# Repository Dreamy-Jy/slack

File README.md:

This is a repo containing all docs related to Slack, a custom plank style keyboard meant for being used while relaxing.

There are 2 prototype revisions planned, each one getting closer to my ideal. Experimental modules will be hosted here as well.

Any revisions pass the second revision will be for refinements.

Why are components rated differently?
- Caps have a voltage rating
- Resistor have a power dissipation rating

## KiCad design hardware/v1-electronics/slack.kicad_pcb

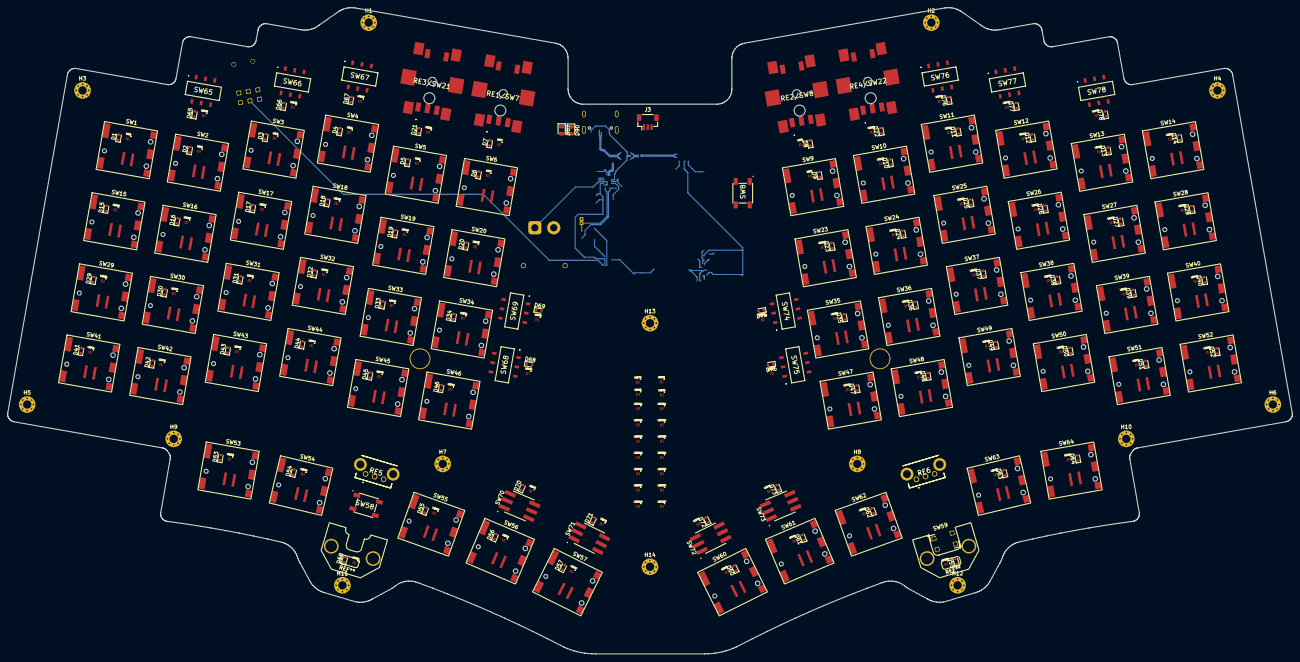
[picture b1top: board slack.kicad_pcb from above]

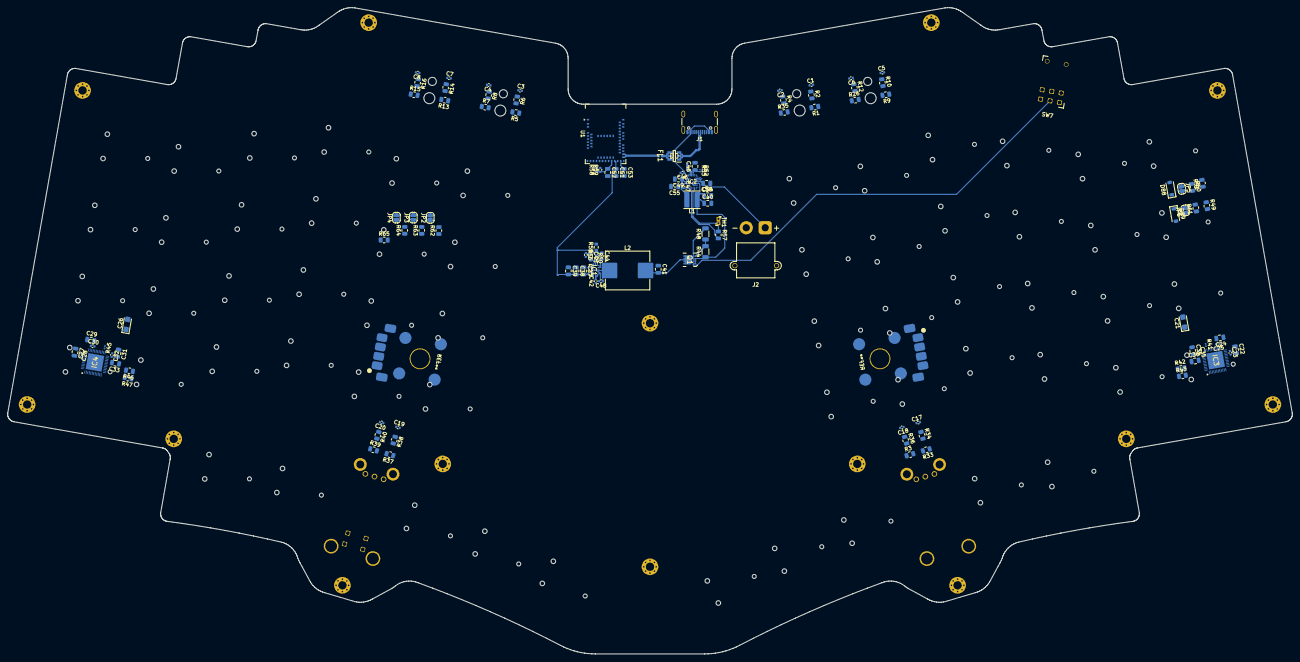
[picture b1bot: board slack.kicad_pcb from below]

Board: 4 copper layers, 338.9 x 170.5 mm, 388 parts (116 on the bottom side), 215 nets.

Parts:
C1, C2, C3, C4, C5, C6, C7, C8, C17, C18, C19, C20: 0.01μF; C_0402_1005Metric
C21, C26: 22μF; CP_EIA-3216-18_Kemet-A
C22, C24, C27, C29, C31, C33, C34, C36: 0.47μF; C_0805_2012Metric
C23, C25, C28, C30, C32, C35, C42, C48: 0.1μF; C_0402_1005Metric
C37, C38, C39: 22μF; C_0805_2012Metric
C40, C41, C49, C50, C51, C52, C53, C54, C55: 10μF; C_0805_2012Metric
C43: 1μF; C_0402_1005Metric
C44: 2.20μF; C_0603_1608Metric
C45: 2.2nF; C_0603_1608Metric
C46: 4.7μF; C_0805_2012Metric
C47: 22nF; C_0402_1005Metric
D0: USBLC6-2SC6; SOT95P280X145-6N
D1, D2, D3, D4, D5, D6, D7, D8, D9, D10, D11, D12, D13, D14, D15, D16, D17, D18, D19, D20, D21, D22, D23, D24, D25, D26, D27, D28, D29, D30, D31, D32, D33, D34, D35, D36, D37, D38, D39, D40, D41, D42, D43, D44, D45, D46, D47, D48, D49, D50, D51, D52, D53, D54, D55, D56, D57, D58, D59, D60, D61, D62, D63, D64, D65, D66, D67, D68, D69, D70, D71, D72, D73, D74, D75, D76, D77, D78: BAS16TS; D_SOD-523
D87, D90: LED_Small_Filled; LED_0805_2012Metric
D88, D89: 3.6V; D_SOD-123
FL1: EXC14CE900U
H1, H2, H3, H4, H5, H6, H7, H8, H9, H10, H11, H12, H13, H14: MountingHole_2.2mm_M2_Pad_Via
IC1: TPS61288LRQQR; PTPS61288RQQR
IC2: MP2721GRH-0000-Z; QFN-22_MP2721_MNP
IC3, IC4: IS31FL3733-QFLS4-TR; QFN40P600X600X80-49N-D
J1: USB4105-GF-A-120; USB_C_Receptacle_GCT_USB4105-xx-A_16P_TopMnt_Horizontal
J2: XT30PW-M; AMASS_XT30PW-M_1x02_P2.50mm_Horizontal_Tight
J3: Female JST-SH; JST_SH_BM03B-SRSS-TB_1x03-1MP_P1.00mm_Vertical
JP2, JP3, JP4, JP5, JP6: Jumper_2_Small_Open; SolderJumper-2_P1.3mm_Open_RoundedPad1.0x1.5mm
L1: 1μH; L_Changjiang_FTC404030S
L2: 2.20μH; L_Sunlord_MWSA1005S
LED1, LED2, LED3, LED4, LED5, LED6, LED7, LED8, LED9, LED10, LED11, LED12, LED13, LED14, LED15, LED16, LED17, LED18, LED19, LED20, LED21, LED22, LED23, LED24, LED25, LED26, LED27, LED28, LED29, LED30, LED31, LED32, LED33, LED34, LED35, LED36, LED37, LED38, LED39, LED40, LED41, LED42, LED43, LED44, LED45, LED46, LED47, LED48, LED49, LED50, LED51, LED52, LED53, LED54, LED55, LED56, LED57, LED58, LED59, LED60, LED61, LED62, LED63, LED64, LED65, LED66, LED67, LED68, LED69, LED70, LED71, LED72, LED73, LED74, LED75, LED76, LED77, LED78, LED79, LED80, LED81, LED82, LED511, LED512, LED513, LED514, LED515, LED517, LED518, LED521, LED522, LED523, LED524, LED525, LED526, LED527: LTST-FC12WEGBD-5A; LTSTFC12WEGBD5A
Q1: AON7423
R1, R2, R3, R4, R5, R6, R7, R8, R9, R10, R12, R13, R14, R15, R16, R26, R33, R34, R35, R36, R37, R38, R39, R40, R57: 10kΩ; R_0805_2012Metric
R41, R45: 22kΩ; R_0201_0603Metric
R42, R43, R46, R47: 100kΩ; R_0805_2012Metric
R44: 100kΩ; R_1206_3216Metric
R48: 1kΩ; R_1206_3216Metric
R49, R51: 5.1kΩ ≤1%; R_0805_2012Metric
R50: 22kΩ; R_0402_1005Metric
R52, R53: 1kΩ; R_01005_0402Metric
R55: 3kΩ; R_0603_1608Metric
R56: 15kΩ; R_0402_1005Metric
R58, R59: 10kΩ; R_0402_1005Metric
R60, R61, R63, R65: 10kΩ ≤1%; R_0805_2012Metric
R62: 4.7kΩ ≤1%; R_0805_2012Metric
R64: 22kΩ ≤1%; R_0805_2012Metric
RE1/SW7, RE2/SW8, RE3/SW21, RE4/SW22: PEC11S-929K-S0015; PEC11S929KS0015
RE5, RE6: EC10E1220505
SW1, SW2, SW3, SW4, SW5, SW6, SW9, SW10, SW11, SW12, SW13, SW14, SW15, SW16, SW17, SW18, SW19, SW20, SW23, SW24, SW25, SW26, SW27, SW28, SW29, SW30, SW31, SW32, SW33, SW34, SW35, SW36, SW37, SW38, SW39, SW40, SW41, SW42, SW43, SW44, SW45, SW46, SW47, SW48, SW49, SW50, SW51, SW52, SW53, SW54, SW55, SW56, SW57, SW60, SW61, SW62, SW63, SW64: MSwitch; Cherry_ULP_SMD
SW7: 2TED3M6RES
SW8, SW58: SW_Push; SKQGAKE010
SW59: SW_Push; TC-1109-C-E
SW65, SW66, SW67, SW68, SW69, SW74, SW75, SW76, SW77, SW78: SS-3235S-L3; SS3235SL3
SW70, SW71, SW72, SW73: BTSA-L-S-8
TH1: 10kΩ @ 25°C; NTCLE413E2103F102L
U1: MDBT50Q-1MV2; Raytac_MDBT50Q

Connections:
+5V: C21.1, C22.2, C23.2, C24.2, C25.2, C26.1, C27.2, C28.2, C29.2, C30.2, C31.2, C32.2, C34.2, C35.2, C37.2, C38.2, C39.2, C51.1, IC1.5 (VOUT), IC3.20 (PVCC_1), IC3.29 (PVCC_2), IC3.37 (AVCC), IC3.38 (DVCC), IC4.20 (PVCC_1), IC4.29 (PVCC_2), IC4.37 (AVCC), IC4.38 (DVCC), R50.1, U1.30 (VDDH)
/LED Matricies/Chip1CurrentSource1: IC3.16 (CS1), LED1.5 (ANODE), LED2.5 (ANODE), LED3.5 (ANODE)
/LED Matricies/Chip1CurrentSource2: IC3.17 (CS2), LED4.5 (ANODE), LED5.5 (ANODE), LED6.5 (ANODE)
/LED Matricies/Chip1CurrentSource3: IC3.18 (CS3), LED7.5 (ANODE), LED15.5 (ANODE), LED16.5 (ANODE)
/LED Matricies/Chip1CurrentSource4: IC3.19 (CS4), LED17.5 (ANODE), LED18.5 (ANODE), LED19.5 (ANODE)
/LED Matricies/Chip1CurrentSource5: IC3.21 (CS5), LED20.5 (ANODE), LED21.5 (ANODE), LED29.5 (ANODE)
/LED Matricies/Chip1CurrentSource6: IC3.22 (CS6), LED30.5 (ANODE), LED31.5 (ANODE), LED32.5 (ANODE)
/LED Matricies/Chip1CurrentSource7: IC3.23 (CS7), LED33.5 (ANODE), LED34.5 (ANODE), LED41.5 (ANODE)
/LED Matricies/Chip1CurrentSource8: IC3.24 (CS8), LED42.5 (ANODE), LED43.5 (ANODE), LED44.5 (ANODE)
/LED Matricies/Chip1CurrentSource9: IC3.25 (CS9), LED45.5 (ANODE), LED46.5 (ANODE), LED53.5 (ANODE)
/LED Matricies/Chip1CurrentSource10: IC3.26 (CS10), LED54.5 (ANODE), LED55.5 (ANODE), LED56.5 (ANODE)
/LED Matricies/Chip1CurrentSource11: IC3.27 (CS11), LED57.5 (ANODE), LED58.5 (ANODE), LED65.5 (ANODE)
/LED Matricies/Chip1CurrentSource12: IC3.28 (CS12), LED66.5 (ANODE), LED67.5 (ANODE), LED68.5 (ANODE)
/LED Matricies/Chip1CurrentSource13: IC3.30 (CS13), LED69.5 (ANODE), LED70.5 (ANODE), LED71.5 (ANODE)
/LED Matricies/Chip1CurrentSource14: IC3.31 (CS14), LED79.5 (ANODE), LED80.5 (ANODE), LED511.5 (ANODE)
/LED Matricies/Chip1CurrentSource15: IC3.32 (CS15), LED512.5 (ANODE), LED513.5 (ANODE), LED514.5 (ANODE)
/LED Matricies/Chip1CurrentSource16: IC3.33 (CS16), LED515.5 (ANODE), LED517.5 (ANODE), LED518.5 (ANODE)
/LED Matricies/Chip1I2C_Reset: IC3.47 (IICRST), R43.2
/LED Matricies/Chip1Shutdown: IC3.46 (SDB), R42.2, U1.8 (P1.15)
/LED Matricies/Chip1SinkSwitch1: IC3.2 (SW1), LED1.1 (BLUE), LED4.1 (BLUE), LED7.1 (BLUE), LED17.1 (BLUE), LED20.1 (BLUE), LED30.1 (BLUE), LED33.1 (BLUE), LED42.1 (BLUE), LED45.1 (BLUE), LED54.1 (BLUE), LED57.1 (BLUE), LED66.1 (BLUE), LED69.1 (BLUE), LED79.1 (BLUE), LED512.1 (BLUE), LED515.1 (BLUE)
/LED Matricies/Chip1SinkSwitch2: IC3.3 (SW2), LED1.2 (GREEN), LED4.2 (GREEN), LED7.2 (GREEN), LED17.2 (GREEN), LED20.2 (GREEN), LED30.2 (GREEN), LED33.2 (GREEN), LED42.2 (GREEN), LED45.2 (GREEN), LED54.2 (GREEN), LED57.2 (GREEN), LED66.2 (GREEN), LED69.2 (GREEN), LED79.2 (GREEN), LED512.2 (GREEN), LED515.2 (GREEN)
/LED Matricies/Chip1SinkSwitch3: IC3.4 (SW3), LED1.3 (RED), LED4.3 (RED), LED7.3 (RED), LED17.3 (RED), LED20.3 (RED), LED30.3 (RED), LED33.3 (RED), LED42.3 (RED), LED45.3 (RED), LED54.3 (RED), LED57.3 (RED), LED66.3 (RED), LED69.3 (RED), LED79.3 (RED), LED512.3 (RED), LED515.3 (RED)
/LED Matricies/Chip1SinkSwitch4: IC3.6 (SW4), LED1.4 (WHITE), LED4.4 (WHITE), LED7.4 (WHITE), LED17.4 (WHITE), LED20.4 (WHITE), LED30.4 (WHITE), LED33.4 (WHITE), LED42.4 (WHITE), LED45.4 (WHITE), LED54.4 (WHITE), LED57.4 (WHITE), LED66.4 (WHITE), LED69.4 (WHITE), LED79.4 (WHITE), LED512.4 (WHITE), LED515.4 (WHITE)
/LED Matricies/Chip1SinkSwitch5: IC3.7 (SW5), LED2.1 (BLUE), LED5.1 (BLUE), LED15.1 (BLUE), LED18.1 (BLUE), LED21.1 (BLUE), LED31.1 (BLUE), LED34.1 (BLUE), LED43.1 (BLUE), LED46.1 (BLUE), LED55.1 (BLUE), LED58.1 (BLUE), LED67.1 (BLUE), LED70.1 (BLUE), LED80.1 (BLUE), LED513.1 (BLUE), LED517.1 (BLUE)
/LED Matricies/Chip1SinkSwitch6: IC3.8 (SW6), LED2.2 (GREEN), LED5.2 (GREEN), LED15.2 (GREEN), LED18.2 (GREEN), LED21.2 (GREEN), LED31.2 (GREEN), LED34.2 (GREEN), LED43.2 (GREEN), LED46.2 (GREEN), LED55.2 (GREEN), LED58.2 (GREEN), LED67.2 (GREEN), LED70.2 (GREEN), LED80.2 (GREEN), LED513.2 (GREEN), LED517.2 (GREEN)
/LED Matricies/Chip1SinkSwitch7: IC3.9 (SW7), LED2.3 (RED), LED5.3 (RED), LED15.3 (RED), LED18.3 (RED), LED21.3 (RED), LED31.3 (RED), LED34.3 (RED), LED43.3 (RED), LED46.3 (RED), LED55.3 (RED), LED58.3 (RED), LED67.3 (RED), LED70.3 (RED), LED80.3 (RED), LED513.3 (RED), LED517.3 (RED)
/LED Matricies/Chip1SinkSwitch8: IC3.10 (SW8), LED2.4 (WHITE), LED5.4 (WHITE), LED15.4 (WHITE), LED18.4 (WHITE), LED21.4 (WHITE), LED31.4 (WHITE), LED34.4 (WHITE), LED43.4 (WHITE), LED46.4 (WHITE), LED55.4 (WHITE), LED58.4 (WHITE), LED67.4 (WHITE), LED70.4 (WHITE), LED80.4 (WHITE), LED513.4 (WHITE), LED517.4 (WHITE)
/LED Matricies/Chip1SinkSwitch9: IC3.11 (SW9), LED3.1 (BLUE), LED6.1 (BLUE), LED16.1 (BLUE), LED19.1 (BLUE), LED29.1 (BLUE), LED32.1 (BLUE), LED41.1 (BLUE), LED44.1 (BLUE), LED53.1 (BLUE), LED56.1 (BLUE), LED65.1 (BLUE), LED68.1 (BLUE), LED71.1 (BLUE), LED511.1 (BLUE), LED514.1 (BLUE), LED518.1 (BLUE)
/LED Matricies/Chip1SinkSwitch10: IC3.13 (SW10), LED3.2 (GREEN), LED6.2 (GREEN), LED16.2 (GREEN), LED19.2 (GREEN), LED29.2 (GREEN), LED32.2 (GREEN), LED41.2 (GREEN), LED44.2 (GREEN), LED53.2 (GREEN), LED56.2 (GREEN), LED65.2 (GREEN), LED68.2 (GREEN), LED71.2 (GREEN), LED511.2 (GREEN), LED514.2 (GREEN), LED518.2 (GREEN)
/LED Matricies/Chip1SinkSwitch11: IC3.14 (SW11), LED3.3 (RED), LED6.3 (RED), LED16.3 (RED), LED19.3 (RED), LED29.3 (RED), LED32.3 (RED), LED41.3 (RED), LED44.3 (RED), LED53.3 (RED), LED56.3 (RED), LED65.3 (RED), LED68.3 (RED), LED71.3 (RED), LED511.3 (RED), LED514.3 (RED), LED518.3 (RED)
/LED Matricies/Chip1SinkSwitch12: IC3.15 (SW12), LED3.4 (WHITE), LED6.4 (WHITE), LED16.4 (WHITE), LED19.4 (WHITE), LED29.4 (WHITE), LED32.4 (WHITE), LED41.4 (WHITE), LED44.4 (WHITE), LED53.4 (WHITE), LED56.4 (WHITE), LED65.4 (WHITE), LED68.4 (WHITE), LED71.4 (WHITE), LED511.4 (WHITE), LED514.4 (WHITE), LED518.4 (WHITE)
/LED Matricies/Chip2CurrentSource1: IC4.16 (CS1), LED8.5 (ANODE), LED9.5 (ANODE), LED10.5 (ANODE)
/LED Matricies/Chip2CurrentSource2: IC4.17 (CS2), LED11.5 (ANODE), LED12.5 (ANODE), LED13.5 (ANODE)
/LED Matricies/Chip2CurrentSource3: IC4.18 (CS3), LED14.5 (ANODE), LED22.5 (ANODE), LED23.5 (ANODE)
/LED Matricies/Chip2CurrentSource4: IC4.19 (CS4), LED24.5 (ANODE), LED25.5 (ANODE), LED26.5 (ANODE)
/LED Matricies/Chip2CurrentSource5: IC4.21 (CS5), LED27.5 (ANODE), LED28.5 (ANODE), LED35.5 (ANODE)
/LED Matricies/Chip2CurrentSource6: IC4.22 (CS6), LED36.5 (ANODE), LED37.5 (ANODE), LED38.5 (ANODE)
/LED Matricies/Chip2CurrentSource7: IC4.23 (CS7), LED39.5 (ANODE), LED40.5 (ANODE), LED47.5 (ANODE)
/LED Matricies/Chip2CurrentSource8: IC4.24 (CS8), LED48.5 (ANODE), LED49.5 (ANODE), LED50.5 (ANODE)
/LED Matricies/Chip2CurrentSource9: IC4.25 (CS9), LED51.5 (ANODE), LED52.5 (ANODE), LED59.5 (ANODE)
/LED Matricies/Chip2CurrentSource10: IC4.26 (CS10), LED60.5 (ANODE), LED61.5 (ANODE), LED62.5 (ANODE)
/LED Matricies/Chip2CurrentSource11: IC4.27 (CS11), LED63.5 (ANODE), LED64.5 (ANODE), LED72.5 (ANODE)
/LED Matricies/Chip2CurrentSource12: IC4.28 (CS12), LED73.5 (ANODE), LED74.5 (ANODE), LED75.5 (ANODE)
/LED Matricies/Chip2CurrentSource13: IC4.30 (CS13), LED76.5 (ANODE), LED77.5 (ANODE), LED78.5 (ANODE)
/LED Matricies/Chip2CurrentSource14: IC4.31 (CS14), LED81.5 (ANODE), LED82.5 (ANODE), LED521.5 (ANODE)
/LED Matricies/Chip2CurrentSource15: IC4.32 (CS15), LED522.5 (ANODE), LED523.5 (ANODE), LED524.5 (ANODE)
/LED Matricies/Chip2CurrentSource16: IC4.33 (CS16), LED525.5 (ANODE), LED526.5 (ANODE), LED527.5 (ANODE)
/LED Matricies/Chip2I2C_Reset: IC4.47 (IICRST), R47.2
/LED Matricies/Chip2Shutdown: IC4.46 (SDB), R46.2, U1.47 (P1.00)
/LED Matricies/Chip2SinkSwitch1: IC4.2 (SW1), LED8.1 (BLUE), LED11.1 (BLUE), LED14.1 (BLUE), LED24.1 (BLUE), LED27.1 (BLUE), LED36.1 (BLUE), LED39.1 (BLUE), LED48.1 (BLUE), LED51.1 (BLUE), LED60.1 (BLUE), LED63.1 (BLUE), LED73.1 (BLUE), LED76.1 (BLUE), LED81.1 (BLUE), LED522.1 (BLUE), LED525.1 (BLUE)
/LED Matricies/Chip2SinkSwitch2: IC4.3 (SW2), LED8.2 (GREEN), LED11.2 (GREEN), LED14.2 (GREEN), LED24.2 (GREEN), LED27.2 (GREEN), LED36.2 (GREEN), LED39.2 (GREEN), LED48.2 (GREEN), LED51.2 (GREEN), LED60.2 (GREEN), LED63.2 (GREEN), LED73.2 (GREEN), LED76.2 (GREEN), LED81.2 (GREEN), LED522.2 (GREEN), LED525.2 (GREEN)
/LED Matricies/Chip2SinkSwitch3: IC4.4 (SW3), LED8.3 (RED), LED11.3 (RED), LED14.3 (RED), LED24.3 (RED), LED27.3 (RED), LED36.3 (RED), LED39.3 (RED), LED48.3 (RED), LED51.3 (RED), LED60.3 (RED), LED63.3 (RED), LED73.3 (RED), LED76.3 (RED), LED81.3 (RED), LED522.3 (RED), LED525.3 (RED)
/LED Matricies/Chip2SinkSwitch4: IC4.6 (SW4), LED8.4 (WHITE), LED11.4 (WHITE), LED14.4 (WHITE), LED24.4 (WHITE), LED27.4 (WHITE), LED36.4 (WHITE), LED39.4 (WHITE), LED48.4 (WHITE), LED51.4 (WHITE), LED60.4 (WHITE), LED63.4 (WHITE), LED73.4 (WHITE), LED76.4 (WHITE), LED81.4 (WHITE), LED522.4 (WHITE), LED525.4 (WHITE)
/LED Matricies/Chip2SinkSwitch5: IC4.7 (SW5), LED9.1 (BLUE), LED12.1 (BLUE), LED22.1 (BLUE), LED25.1 (BLUE), LED28.1 (BLUE), LED37.1 (BLUE), LED40.1 (BLUE), LED49.1 (BLUE), LED52.1 (BLUE), LED61.1 (BLUE), LED64.1 (BLUE), LED74.1 (BLUE), LED77.1 (BLUE), LED82.1 (BLUE), LED523.1 (BLUE), LED526.1 (BLUE)
/LED Matricies/Chip2SinkSwitch6: IC4.8 (SW6), LED9.2 (GREEN), LED12.2 (GREEN), LED22.2 (GREEN), LED25.2 (GREEN), LED28.2 (GREEN), LED37.2 (GREEN), LED40.2 (GREEN), LED49.2 (GREEN), LED52.2 (GREEN), LED61.2 (GREEN), LED64.2 (GREEN), LED74.2 (GREEN), LED77.2 (GREEN), LED82.2 (GREEN), LED523.2 (GREEN), LED526.2 (GREEN)
/LED Matricies/Chip2SinkSwitch7: IC4.9 (SW7), LED9.3 (RED), LED12.3 (RED), LED22.3 (RED), LED25.3 (RED), LED28.3 (RED), LED37.3 (RED), LED40.3 (RED), LED49.3 (RED), LED52.3 (RED), LED61.3 (RED), LED64.3 (RED), LED74.3 (RED), LED77.3 (RED), LED82.3 (RED), LED523.3 (RED), LED526.3 (RED)
/LED Matricies/Chip2SinkSwitch8: IC4.10 (SW8), LED9.4 (WHITE), LED12.4 (WHITE), LED22.4 (WHITE), LED25.4 (WHITE), LED28.4 (WHITE), LED37.4 (WHITE), LED40.4 (WHITE), LED49.4 (WHITE), LED52.4 (WHITE), LED61.4 (WHITE), LED64.4 (WHITE), LED74.4 (WHITE), LED77.4 (WHITE), LED82.4 (WHITE), LED523.4 (WHITE), LED526.4 (WHITE)
/LED Matricies/Chip2SinkSwitch9: IC4.11 (SW9), LED10.1 (BLUE), LED13.1 (BLUE), LED23.1 (BLUE), LED26.1 (BLUE), LED35.1 (BLUE), LED38.1 (BLUE), LED47.1 (BLUE), LED50.1 (BLUE), LED59.1 (BLUE), LED62.1 (BLUE), LED72.1 (BLUE), LED75.1 (BLUE), LED78.1 (BLUE), LED521.1 (BLUE), LED524.1 (BLUE), LED527.1 (BLUE)
/LED Matricies/Chip2SinkSwitch10: IC4.13 (SW10), LED10.2 (GREEN), LED13.2 (GREEN), LED23.2 (GREEN), LED26.2 (GREEN), LED35.2 (GREEN), LED38.2 (GREEN), LED47.2 (GREEN), LED50.2 (GREEN), LED59.2 (GREEN), LED62.2 (GREEN), LED72.2 (GREEN), LED75.2 (GREEN), LED78.2 (GREEN), LED521.2 (GREEN), LED524.2 (GREEN), LED527.2 (GREEN)
/LED Matricies/Chip2SinkSwitch11: IC4.14 (SW11), LED10.3 (RED), LED13.3 (RED), LED23.3 (RED), LED26.3 (RED), LED35.3 (RED), LED38.3 (RED), LED47.3 (RED), LED50.3 (RED), LED59.3 (RED), LED62.3 (RED), LED72.3 (RED), LED75.3 (RED), LED78.3 (RED), LED521.3 (RED), LED524.3 (RED), LED527.3 (RED)
/LED Matricies/Chip2SinkSwitch12: IC4.15 (SW12), LED10.4 (WHITE), LED13.4 (WHITE), LED23.4 (WHITE), LED26.4 (WHITE), LED35.4 (WHITE), LED38.4 (WHITE), LED47.4 (WHITE), LED50.4 (WHITE), LED59.4 (WHITE), LED62.4 (WHITE), LED72.4 (WHITE), LED75.4 (WHITE), LED78.4 (WHITE), LED521.4 (WHITE), LED524.4 (WHITE), LED527.4 (WHITE)
/LED Matricies/I2C1.SCL: IC2.16 (SCL), IC3.42 (SCL), IC4.42 (SCL), IC4.44 (ADDR2), R59.2, U1.29 (P0.12)
/LED Matricies/I2C1.SDA: IC2.15 (SDA), IC3.41 (SDA), IC4.41 (SDA), R58.2, U1.27 (P0.11)
/LED Matricies/LED Matrix Controller 1/R_EXT: IC3.35 (R_EXT), R41.2
/LED Matricies/LED Matrix Controller 2/R_EXT: IC4.35 (R_EXT), R45.2
/LED Matricies/Sync: IC3.40 (SYNC), IC4.40 (SYNC)
/LED Matricies/~Chip1Interrupt: IC3.45 (~INTB), JP3.2 (B), R63.2
/LED Matricies/~Chip2Interrupt: IC4.45 (~INTB), JP4.2 (B), R64.2
/MCU/Column1: SW1.1, SW15.1, SW29.1, SW41.1, SW65.2 (COM_1), SW65.5 (COM_2), U1.61 (P1.01)
/MCU/Column2: SW2.1, SW16.1, SW30.1, SW42.1, SW53.1, SW66.2 (COM_1), SW66.5 (COM_2), U1.50 (P1.02)
/MCU/Column3: SW3.1, SW17.1, SW31.1, SW43.1, SW54.1, SW67.2 (COM_1), SW67.5 (COM_2), U1.60 (P1.03)
/MCU/Column4: SW4.1, SW18.1, SW32.1, SW44.1, SW55.1, SW68.2 (COM_1), SW68.5 (COM_2), U1.56 (P1.04)
/MCU/Column5: SW5.1, SW19.1, SW33.1, SW45.1, SW56.1, SW69.2 (COM_1), SW69.5 (COM_2), U1.59 (P1.05)
/MCU/Column6: SW6.1, SW20.1, SW34.1, SW46.1, SW57.1, SW70.2, SW70.5 (2), U1.57 (P1.06)
/MCU/Column7: RE1/SW7.D1 (SI), RE3/SW21.D1 (SI), SW58.1, SW71.2, SW71.5 (2), U1.58 (P1.07)
/MCU/Column8: RE2/SW8.D1 (SI), RE4/SW22.D1 (SI), SW59.1, SW72.2, SW72.5 (2), U1.25 (P1.08)
/MCU/Column9: SW9.1, SW23.1, SW35.1, SW47.1, SW60.1, SW73.2, SW73.5 (2), U1.26 (P1.09)
/MCU/Column10: SW10.1, SW24.1, SW36.1, SW48.1, SW61.1, SW74.2 (COM_1), SW74.5 (COM_2), U1.3 (P1.10)
/MCU/Column11: SW11.1, SW25.1, SW37.1, SW49.1, SW62.1, SW75.2 (COM_1), SW75.5 (COM_2), U1.4 (P1.11)
/MCU/Column12: SW12.1, SW26.1, SW38.1, SW50.1, SW63.1, SW76.2 (COM_1), SW76.5 (COM_2), U1.5 (P1.12)
/MCU/Column13: SW13.1, SW27.1, SW39.1, SW51.1, SW64.1, SW77.2 (COM_1), SW77.5 (COM_2), U1.6 (P1.13)
/MCU/Column14: SW14.1, SW28.1, SW40.1, SW52.1, SW78.2 (COM_1), SW78.5 (COM_2), U1.7 (P1.14)
/MCU/RESET: SW8.2, U1.40 (P0.18)
/MCU/RotaryEncoder_AChannel1: C1.1, R2.1, U1.23 (P0.07)
/MCU/RotaryEncoder_AChannel2: C3.1, R6.1, U1.52 (P0.09)
/MCU/RotaryEncoder_AChannel3: C5.1, R10.2, U1.37 (P0.13)
/MCU/RotaryEncoder_AChannel4: C7.1, R14.2, U1.39 (P0.15)
/MCU/RotaryEncoder_AChannel5: C17.1, R34.1, U1.19 (P0.26)
/MCU/RotaryEncoder_AChannel6: C19.1, R38.1, U1.21 (P0.05)
/MCU/RotaryEncoder_BChannel1: C2.1, R4.1, U1.24 (P0.08)
/MCU/RotaryEncoder_BChannel2: C4.1, R8.1, U1.54 (P0.10)
/MCU/RotaryEncoder_BChannel3: C6.1, R12.1, U1.36 (P0.14)
/MCU/RotaryEncoder_BChannel4: C8.1, R16.1, U1.38 (P0.16)
/MCU/RotaryEncoder_BChannel5: C18.1, R36.1, U1.16 (P0.27)
/MCU/RotaryEncoder_BChannel6: C20.1, R40.2, U1.13 (P0.28)
/MCU/Row1: D1.1 (K), D2.1 (K), D3.1 (K), D4.1 (K), D5.1 (K), D6.1 (K), D7.1 (K), D8.1 (K), D9.1 (K), D10.1 (K), D11.1 (K), D12.1 (K), D13.1 (K), D14.1 (K), U1.17 (P0.00)
/MCU/Row2: D15.1 (K), D16.1 (K), D17.1 (K), D18.1 (K), D19.1 (K), D20.1 (K), D21.1 (K), D22.1 (K), D23.1 (K), D24.1 (K), D25.1 (K), D26.1 (K), D27.1 (K), D28.1 (K), U1.18 (P0.01)
/MCU/Row3: D29.1 (K), D30.1 (K), D31.1 (K), D32.1 (K), D33.1 (K), D34.1 (K), D35.1 (K), D36.1 (K), D37.1 (K), D38.1 (K), D39.1 (K), D40.1 (K), U1.11 (P0.02)
/MCU/Row4: D41.1 (K), D42.1 (K), D43.1 (K), D44.1 (K), D45.1 (K), D46.1 (K), D47.1 (K), D48.1 (K), D49.1 (K), D50.1 (K), D51.1 (K), D52.1 (K), U1.9 (P0.03)
/MCU/Row5: D53.1 (K), D54.1 (K), D55.1 (K), D56.1 (K), D57.1 (K), D58.1 (K), D59.1 (K), D60.1 (K), D61.1 (K), D62.1 (K), D63.1 (K), D64.1 (K), U1.20 (P0.04)
/MCU/Row6: D65.1 (K_1), D66.1 (K_1), D67.1 (K_1), D68.1 (K_1), D69.1 (K_1), D70.1 (K), D71.1 (K), D72.1 (K), D73.1 (K), D74.1 (K_1), D75.1 (K_1), D76.1 (K_1), D77.1 (K_1), D78.1 (K_1), U1.22 (P0.06)
/MCU/SWDCLK: J3.1, U1.53 (SWDCLK)
/MCU/SWDIO: J3.3, U1.51 (SWDIO)
/MCU/USB.CC1: D88.1 (K), JP5.2 (B), R60.2, U1.14 (AIN6)
/MCU/USB.CC2: D89.1 (K), JP6.2 (B), R61.2, U1.12 (AIN7)
/MCU/USB.D+: D0.3 (I/O2), D0.4 (I/O2), FL1.1, FL1.4, IC2.21 (D+), J1.A7 (D-), J1.B7 (D-), U1.35 (D+)
/MCU/USB.D-: D0.1 (I/O1), D0.6 (I/O1), FL1.2, FL1.3, IC2.20 (D-), J1.A6 (D+), J1.B6 (D+), U1.34 (D-)
/MCU/~ChargingChipInterrupt: IC2.8 (~INT), JP2.2 (B), R62.2
/MCU/~INT: JP2.1 (A), JP3.1 (A), JP4.1 (A), R62.1, R63.1, R64.1, R65.2, U1.10 (AIN5)
/Power Train/BATT: C50.1, IC2.12 (BATTSNS), IC2.14 (BATT), J2.1
/Power Train/BST_MP: C47.2, IC2.6 (BST)
/Power Train/BST_TPS: C48.2, IC1.8 (BST)
/Power Train/CC1: J1.A5 (CC1), JP5.1 (A), R51.1, R60.1
/Power Train/CC2: J1.B5 (CC2), JP6.1 (A), R49.1, R61.1
/Power Train/COMP: C45.2, IC1.2 (COMP)
/Power Train/FB: IC1.1 (FB), R50.2, R55.1
/Power Train/NCT1: IC2.10 (NTC1), R57.1, TH1.2
/Power Train/PG/NTC2: D87.1 (K), IC2.9 (PG/NTC2)
/Power Train/PMID: C49.1, C55.1, IC2.3 (PMID)
/Power Train/STAT/IB: D90.1 (K), IC2.11 (STAT/IB)
/Power Train/SW_MP: C47.1, IC2.4 (SW), L1.2
/Power Train/SW_TPS: C48.1, IC1.4 (SW), IC1.9 (SW), L2.1
DGND: C1.2, C2.2, C3.2, C4.2, C5.2, C6.2, C7.2, C8.2, C17.2, C18.2, C19.2, C20.2, C21.2, C22.1, C23.1, C24.1, C25.1, C26.2, C27.1, C28.1, C29.1, C30.1, C31.1, C32.1, C33.1, C34.1, C35.1, C36.1, C37.1, C38.1, C39.1, C40.2, C41.1, C42.1, C43.2, C44.1, C46.2, C49.2, C50.2, C51.2, C52.2, C53.2, C54.2, C55.2, D0.2 (GND), D88.2 (A), D89.2 (A), H1.1, H2.1, H3.1, H4.1, H5.1, H6.1, H7.1, H8.1, H9.1, H10.1, H11.1, H12.1, H13.1, H14.1, IC1.3 (PGND), IC1.10 (AGND), IC2.5 (PGND), IC2.18 (AGND), IC3.5 (PGND_1), IC3.12 (PGND_2), IC3.34 (AGND), IC3.43 (ADDR1), IC3.44 (ADDR2), IC3.48 (GND), IC3.49 (EP), IC4.5 (PGND_1), IC4.12 (PGND_2), IC4.34 (AGND), IC4.43 (ADDR1), IC4.48 (GND), IC4.49 (EP), J1.A1 (GND), J1.A12 (GND), J1.B1 (GND), J1.B12 (GND), J1.SH (SHIELD), J2.2, J2.MP (MountPin), J3.2, J3.MP (MountPin), R41.1, R42.1, R43.1, R45.1, R46.1, R47.1, R49.2, R51.2, R55.2, R56.2, RE1/SW7.C1 (C), RE1/SW7.MP1 (H), RE1/SW7.MP2 (H), RE1/SW7.MP3 (H), RE1/SW7.MP4 (H), RE1/SW7.MP5 (H), RE1/SW7.MP6 (H), RE2/SW8.C1 (C), RE2/SW8.MP1 (H), RE2/SW8.MP2 (H), RE2/SW8.MP3 (H), RE2/SW8.MP4 (H), RE2/SW8.MP5 (H), RE2/SW8.MP6 (H), RE3/SW21.C1 (C), RE3/SW21.MP1 (H), RE3/SW21.MP2 (H), RE3/SW21.MP3 (H), RE3/SW21.MP4 (H), RE3/SW21.MP5 (H), RE3/SW21.MP6 (H), RE4/SW22.C1 (C), RE4/SW22.MP1 (H), RE4/SW22.MP2 (H), RE4/SW22.MP3 (H), RE4/SW22.MP4 (H), RE4/SW22.MP5 (H), RE4/SW22.MP6 (H), RE5.C1 (C), RE5.MH1 (H), RE5.MH2 (H), RE6.C1 (C), RE6.MH1 (H), RE6.MH2 (H), SW7.1 (A), SW7.4 (A), SW8.1, TH1.1, U1.1 (GND), U1.2 (GND), U1.15 (GND), U1.33 (GND), U1.55 (GND)
unnamed: C45.1, R56.1
unnamed: D1.2 (A), SW1.2
unnamed: D2.2 (A), SW2.2
unnamed: D3.2 (A), SW3.2
unnamed: D4.2 (A), SW4.2
unnamed: D5.2 (A), SW5.2
unnamed: D6.2 (A), SW6.2
unnamed: D7.2 (A), RE1/SW7.E1 (SO)
unnamed: D8.2 (A), RE2/SW8.E1 (SO)
unnamed: D9.2 (A), SW9.2
unnamed: D10.2 (A), SW10.2
unnamed: D11.2 (A), SW11.2
unnamed: D12.2 (A), SW12.2
unnamed: D13.2 (A), SW13.2
unnamed: D14.2 (A), SW14.2
unnamed: D15.2 (A), SW15.2
unnamed: D16.2 (A), SW16.2
unnamed: D17.2 (A), SW17.2
unnamed: D18.2 (A), SW18.2
unnamed: D19.2 (A), SW19.2
unnamed: D20.2 (A), SW20.2
unnamed: D21.2 (A), RE3/SW21.E1 (SO)
unnamed: D22.2 (A), RE4/SW22.E1 (SO)
unnamed: D23.2 (A), SW23.2
unnamed: D24.2 (A), SW24.2
unnamed: D25.2 (A), SW25.2
unnamed: D26.2 (A), SW26.2
unnamed: D27.2 (A), SW27.2
unnamed: D28.2 (A), SW28.2
unnamed: D29.2 (A), SW29.2
unnamed: D30.2 (A), SW30.2
unnamed: D31.2 (A), SW31.2
unnamed: D32.2 (A), SW32.2
unnamed: D33.2 (A), SW33.2
unnamed: D34.2 (A), SW34.2
unnamed: D35.2 (A), SW35.2
unnamed: D36.2 (A), SW36.2
unnamed: D37.2 (A), SW37.2
unnamed: D38.2 (A), SW38.2
unnamed: D39.2 (A), SW39.2
unnamed: D40.2 (A), SW40.2
unnamed: D41.2 (A), SW41.2
unnamed: D42.2 (A), SW42.2
unnamed: D43.2 (A), SW43.2
unnamed: D44.2 (A), SW44.2
unnamed: D45.2 (A), SW45.2
unnamed: D46.2 (A), SW46.2
unnamed: D47.2 (A), SW47.2
unnamed: D48.2 (A), SW48.2
unnamed: D49.2 (A), SW49.2
unnamed: D50.2 (A), SW50.2
unnamed: D51.2 (A), SW51.2
unnamed: D52.2 (A), SW52.2
unnamed: D53.2 (A), SW53.2
unnamed: D54.2 (A), SW54.2
unnamed: D55.2 (A), SW55.2
unnamed: D56.2 (A), SW56.2
unnamed: D57.2 (A), SW57.2
unnamed: D58.2 (A), SW58.2
unnamed: D59.2 (A), SW59.2
unnamed: D60.2 (A), SW60.2
unnamed: D61.2 (A), SW61.2
unnamed: D62.2 (A), SW62.2
unnamed: D63.2 (A), SW63.2
unnamed: D64.2 (A), SW64.2
unnamed: D70.2 (A), SW70.3, SW70.6 (3)
unnamed: D71.2 (A), SW71.3, SW71.6 (3)
unnamed: D72.2 (A), SW72.3, SW72.6 (3)
unnamed: D73.2 (A), SW73.3, SW73.6 (3)
unnamed: D87.2 (A), R53.1
unnamed: D90.2 (A), R52.1
unnamed: C44.2, IC1.11 (VCC)
unnamed: Q1.4 (G), R44.2, R48.1
unnamed: R48.2, SW7.2 (B), SW7.5 (B)
unnamed: R1.2, R2.2, RE1/SW7.A1 (A)
unnamed: R4.2, R35.2, RE1/SW7.B1 (B)
unnamed: R5.2, R6.2, RE2/SW8.A1 (A)
unnamed: R7.2, R8.2, RE2/SW8.B1 (B)
unnamed: R9.2, R10.1, RE3/SW21.A1 (A)
unnamed: R12.2, R26.1, RE3/SW21.B1 (B)
unnamed: R13.2, R14.1, RE4/SW22.A1 (A)
unnamed: R15.1, R16.2, RE4/SW22.B1 (B)
unnamed: R33.2, R34.2, RE5.A1 (A)
unnamed: R3.2, R36.2, RE5.B1 (B)
unnamed: R37.2, R38.2, RE6.A1 (A)
unnamed: R39.2, R40.1, RE6.B1 (B)
VCC: C46.1, IC2.19 (VCC), R52.2, R53.2
VRNTC: IC2.7 (VRNTC), R57.2
V_BUS: C43.1, C53.1, D0.5 (VBUS), IC2.2 (IN), J1.A4 (VBUS), J1.A9 (VBUS), J1.B4 (VBUS), J1.B9 (VBUS), U1.32 (VBUS)
V_IN_TPS: C41.2, C42.2, IC1.6 (EN), IC1.7 (VIN), L2.2, Q1.5 (D)
V_OUT_MP: C40.1, C54.1, IC2.13 (SYS), L1.1, Q1.1 (S), Q1.2 (S), Q1.3 (S), R44.1
V_REG0: C33.2, C36.2, C52.1, IC3.39 (VIO), IC4.39 (VIO), R1.1, R3.1, R5.1, R7.1, R9.1, R13.1, R15.2, R26.2, R33.1, R35.1, R37.1, R39.1, R58.1, R59.1, R65.1, U1.28 (VDD)

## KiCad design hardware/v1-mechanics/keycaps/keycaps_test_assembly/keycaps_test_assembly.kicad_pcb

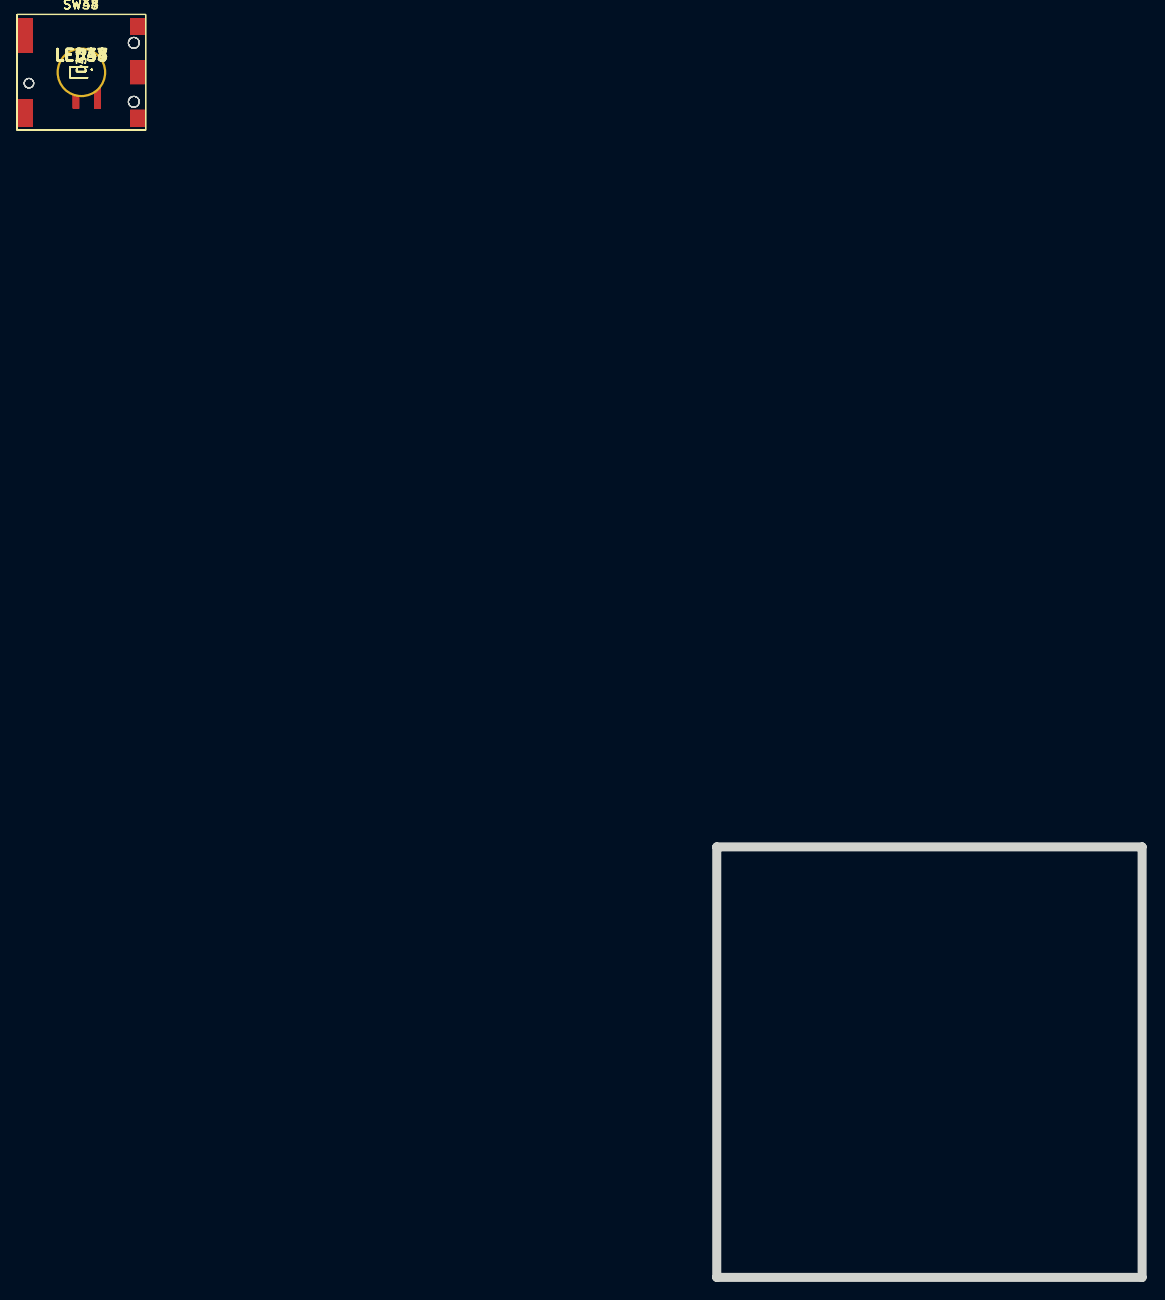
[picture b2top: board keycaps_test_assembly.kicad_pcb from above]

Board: 2 copper layers, 47.0 x 47.6 mm, 12 parts (0 on the bottom side), 14 nets, no tracks yet.

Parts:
D33, D34, D47, D48: D; D_SOD-523
LED33, LED34, LED47, LED48: LTST-FC12WEGBD-5A; LTSTFC12WEGBD5A
SW33, SW34, SW47, SW48: MSwitch; Cherry_ULP_SMD

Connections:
/LED Matricies/Chip1CurrentSource7: LED33.5 (ANODE), LED34.5 (ANODE)
/LED Matricies/Chip1CurrentSource9: LED47.5 (ANODE), LED48.5 (ANODE)
/LED Matricies/Chip1SinkSwitch5: LED34.1 (BLUE), LED47.1 (BLUE)
/LED Matricies/Chip1SinkSwitch6: LED34.2 (GREEN), LED47.2 (GREEN)
/LED Matricies/Chip1SinkSwitch7: LED34.3 (RED), LED47.3 (RED)
/LED Matricies/Chip1SinkSwitch8: LED34.4 (WHITE), LED47.4 (WHITE)
/MCU/Column5: SW33.1, SW47.1
/MCU/Column6: SW34.1, SW48.1
/MCU/Row3: D33.1 (K), D34.1 (K)
/MCU/Row4: D47.1 (K), D48.1 (K)
unnamed: D33.2 (A), SW33.2
unnamed: D34.2 (A), SW34.2
unnamed: D47.2 (A), SW47.2
unnamed: D48.2 (A), SW48.2

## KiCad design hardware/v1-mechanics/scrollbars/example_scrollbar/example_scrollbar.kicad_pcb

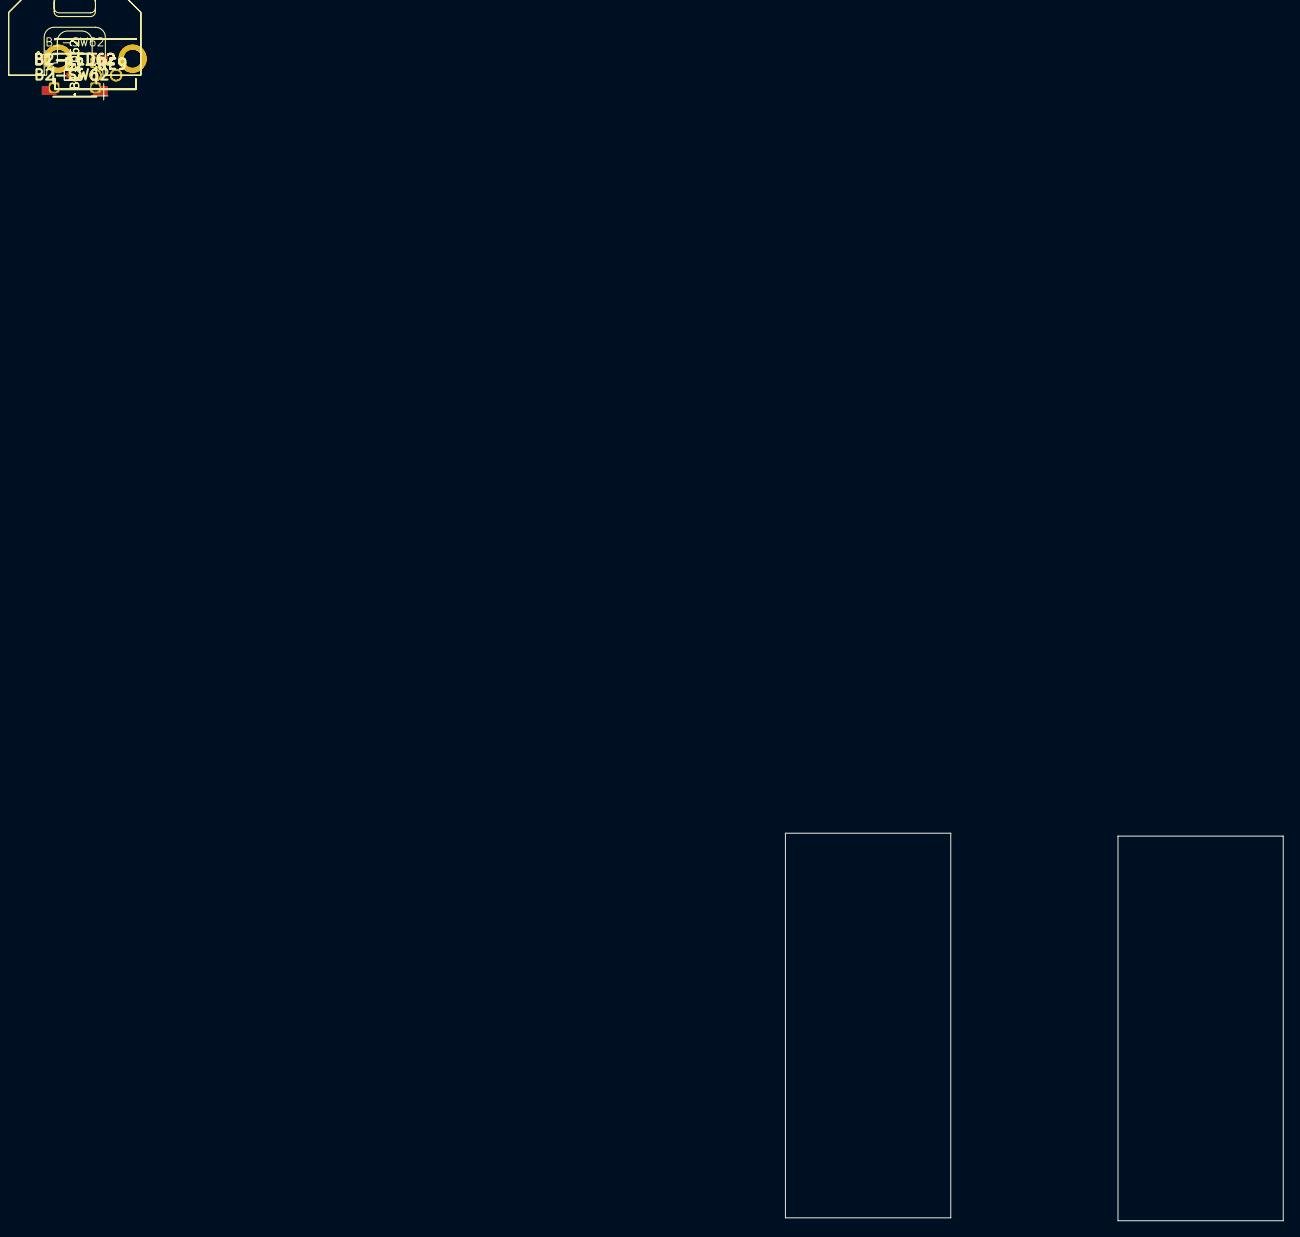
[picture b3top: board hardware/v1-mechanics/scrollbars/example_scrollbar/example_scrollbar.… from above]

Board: 2 copper layers, 10 parts (0 on the bottom side), 11 nets, no tracks yet.

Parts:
B1-D62, B2-D62: D; D_SOD-523
B1-LED62, B2-LED62: LTST-FC12WEGBD-5A; LTSTFC12WEGBD5A
B1-MP**: switched_grounded_scrollcap
B1-RE9, B2-RE9: EC10E1220505
B1-SW62: SW_Push; TC-1109-C-E
B2-MP**: grounded_scrollcap
B2-SW62: SW_Push; SKQGAKE010

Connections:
/LED Matricies/Chip1CurrentSource12: B1-LED62.5 (ANODE), B2-LED62.5 (ANODE)
/LED Matricies/Chip1SinkSwitch1: B1-LED62.1 (BLUE), B2-LED62.1 (BLUE)
/LED Matricies/Chip1SinkSwitch2: B1-LED62.2 (GREEN), B2-LED62.2 (GREEN)
/LED Matricies/Chip1SinkSwitch3: B1-LED62.3 (RED), B2-LED62.3 (RED)
/LED Matricies/Chip1SinkSwitch4: B1-LED62.4 (WHITE), B2-LED62.4 (WHITE)
/MCU/Column7: B1-SW62.1, B2-SW62.1 (1_1), B2-SW62.4 (1_1)
/MCU/Row5: B1-D62.1 (K), B2-D62.1 (K)
DGND: B1-RE9.C1 (C), B1-RE9.MH1 (H), B1-RE9.MH2 (H), B2-RE9.C1 (C), B2-RE9.MH1 (H), B2-RE9.MH2 (H)
unnamed: B1-D62.2 (A), B1-SW62.2, B2-D62.2 (A), B2-SW62.2 (2_2), B2-SW62.3 (2_2)
unnamed: B1-RE9.A1 (A), B2-RE9.A1 (A)
unnamed: B1-RE9.B1 (B), B2-RE9.B1 (B)

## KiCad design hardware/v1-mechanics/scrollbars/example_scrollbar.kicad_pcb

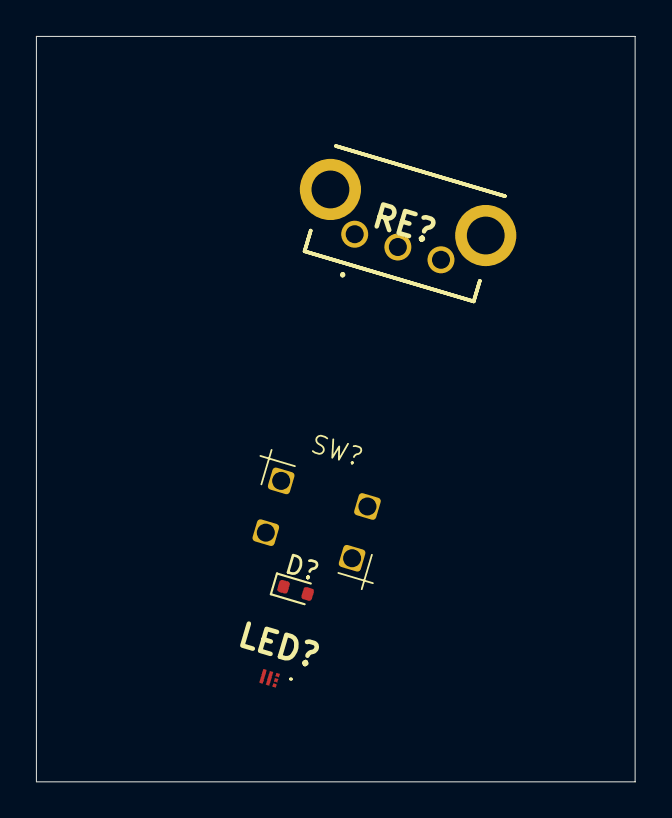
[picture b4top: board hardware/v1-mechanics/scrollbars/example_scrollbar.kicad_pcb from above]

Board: 2 copper layers, 33.3 x 41.4 mm, 4 parts (0 on the bottom side), 2 nets, no tracks yet.

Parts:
D?: D; D_SOD-523
LED?: LTST-FC12WEGBD-5A; LTSTFC12WEGBD5A
RE?: EC10E1220505
SW?: SW_Push; TC-1109-C-E

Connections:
DGND: RE?.C1 (C), RE?.MH1 (H), RE?.MH2 (H)
unnamed: D?.2 (A), SW?.2
